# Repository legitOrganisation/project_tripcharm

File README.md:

# project_tripcharm

Github Repository containing all technical files in regard to our project.

v1-no-audio branch has been deprecated and merged to main branch.

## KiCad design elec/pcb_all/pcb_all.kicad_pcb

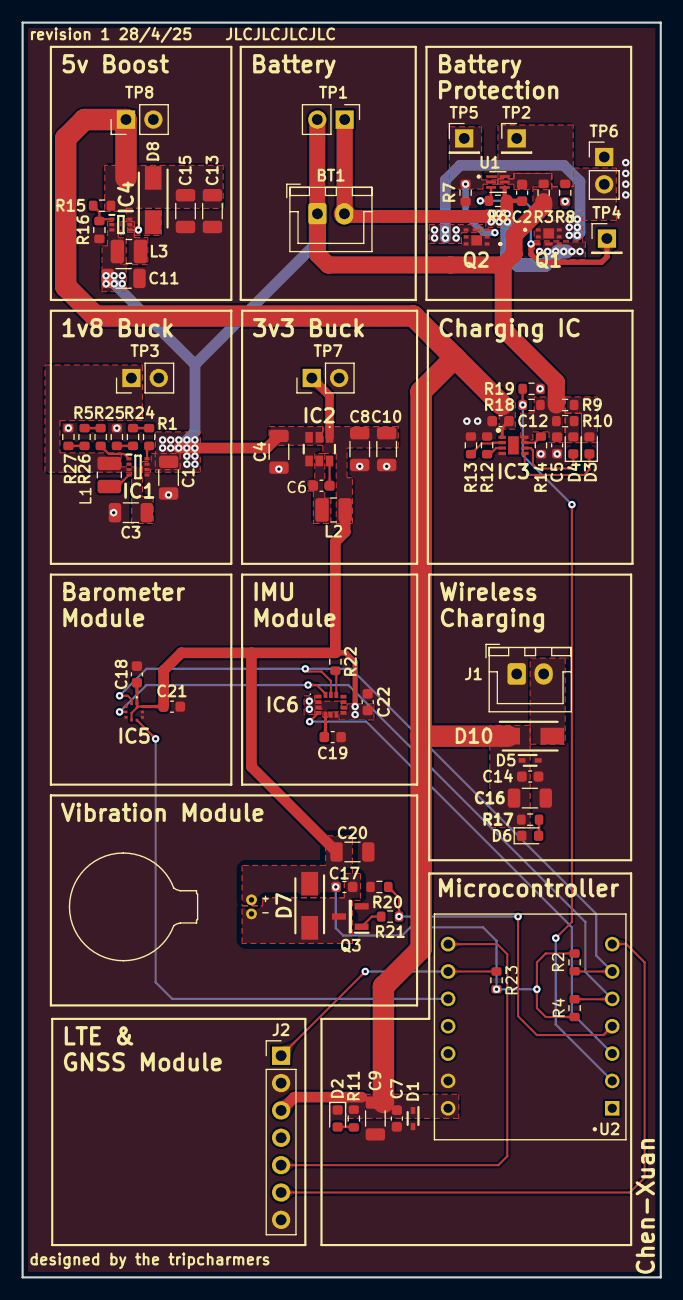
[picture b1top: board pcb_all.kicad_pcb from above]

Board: 2 copper layers, 59.2 x 116.5 mm, 84 parts (0 on the bottom side), 45 nets.

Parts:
B1: HD-EMC1003-3-LW27; PUI_HD-EMC1003-3-LW27
BT1: Battery_Cell; JST_XH_B2B-XH-A_1x02_P2.50mm_Vertical
C1: 4.7uF; C_1206_3216Metric
C2, C6, C7, C14, C17, C18, C19, C21, C22: 100nF; C_0603_1608Metric
C3, C8, C10, C13, C15, C20: 22uF; C_1206_3216Metric
C4, C9, C11, C16: 10uF; C_1206_3216Metric
C5, C12: 1uF; C_0603_1608Metric
D1, D5: ESD7351XV2T1G; SODFL1608X70N
D2, D3, D4, D6: LED; LED_0603_1608Metric
D7, D8, D10: SS14-M3_5AT; DIOM5127X229N
IC1: TPS629203QDRLRQ1; SOTFL50P160X60-8N
IC2: AP63203WU-7; AP63203WU7
IC3: BQ25176MDSGR; SON50P200X200X80-9N
IC4: TPS61023DRLR; SOTFL50P160X60-6N
IC5: BMP390
IC6: LSM6DSLTR
J1: Conn_01x02; JST_XH_B2B-XH-A_1x02_P2.50mm_Vertical
J2: Conn_01x07; PinHeader_1x07_P2.54mm_Vertical
L1: 2.2uH; L_1008_2520Metric
L2: 4.7uH; L_1008_2520Metric
L3: 1uH; L_1008_2520Metric
Q1, Q2: CSD16301Q2
Q3: IRLML6344TRPBF; SOT95P237X112-3N
R1, R5, R26: 30k; R_0603_1608Metric
R2, R4, R22, R27: 4.7k; R_0603_1608Metric
R3: R330; R_0603_1608Metric
R6, R7: 5.1M; R_0603_1608Metric
R8: 2.2K; R_0603_1608Metric
R9, R10, R12, R18, R20, R23: 10k; R_0603_1608Metric
R11, R17: 680R; R_0603_1608Metric
R13: 604R; R_0603_1608Metric
R14: 24.3k; R_0603_1608Metric
R15: 68k; R_0603_1608Metric
R16: 510k; R_0603_1608Metric
R19: 1k; R_0603_1608Metric
R21: 100R; R_0603_1608Metric
R24, R25: 2k; R_0603_1608Metric
TP1, TP3, TP6, TP7, TP8: TestPoint_2Pole; PinHeader_1x02_P2.54mm_Vertical
TP2, TP4, TP5: TestPoint; PinHeader_1x01_P2.54mm_Vertical
U1: BQ29700DSER; SON50P150X150X80-6N
U2: Xiao_ESP32-C3

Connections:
+1V8: C3.1, IC1.3 (VOS), L1.2, TP3.1
+3V3: B1.P, C8.1, C10.1, C17.1, C18.1, C19.1, C20.1, C21.1, C22.1, D7.1 (K), IC2.1 (FB), IC5.1 (VDDIO), IC5.6 (CSB), IC5.10 (VDD), IC6.2 (SDX), IC6.3 (SCX), IC6.5 (VDDIO), IC6.8 (VDD), L2.2, R2.1, R4.1, R22.1, R23.2, TP7.1
+5V: C7.1, C9.1, C12.1, C13.1, C14.1, C15.1, C16.1, D1.1 (K), D5.1 (K), D8.1 (K), D10.1 (K), IC3.1 (IN), J2.3, R11.1, R15.1, R17.1, TP8.1, U2.14 (VUSB)
+BATT: BT1.1 (+), C1.1, C4.1, C5.1, C11.1, IC1.6 (VIN), IC1.7 (EN), IC2.2 (EN), IC2.3 (VIN), IC3.8 (OUT), IC4.2 (EN), IC4.3 (VIN), L3.1, R3.1, R9.1, R10.1, R18.1, TP1.2, TP6.2
/BATT VOLTAGE: R18.2, R19.1, U2.2 (D1)
/INT1 (IMU): IC6.4 (INT1), U2.3 (D2)
/INT (BAROMETER): IC5.7 (INT), U2.10 (D9)
/PWM (Vibration): R20.1, R21.1, U2.4 (D3)
/RX (SIM7600G-H): J2.6, U2.7 (TX_D6)
/SCL: IC5.2 (SCK), IC6.13 (SCL), R2.2, U2.6 (D5)
/SDA: IC5.4 (SDI), IC6.14 (SDA), R4.2, U2.5 (D4)
/SLEEP (SIM7600G-H): J2.1, R23.1, U2.9 (D8)
/TX (SIM7600G-H): J2.5, U2.8 (RX_D7)
GND: C1.2, C3.2, C4.2, C5.2, C7.2, C8.2, C9.2, C10.2, C11.2, C12.2, C13.2, C14.2, C15.2, C16.2, C18.2, C19.2, C20.2, C21.2, C22.2, D1.2 (A), D2.1 (K), D5.2 (A), D6.1 (K), IC1.5 (GND), IC2.4 (GND), IC3.4 (GND), IC4.4 (GND), IC5.3 (VSS_1), IC5.5 (SDO), IC5.8 (VSS_2), IC5.9 (VSS_3), IC6.1 (SDO/SA0), IC6.6 (GND_1), IC6.7 (GND_2), J1.1, J2.2, J2.7, Q2.2 (D), Q3.2 (S), R7.2, R8.2, R12.2, R13.2, R14.2, R16.2, R19.2, R20.2, R25.2, R27.2, TP3.2, TP6.1, TP7.2, TP8.2, U2.13 (GND)
unnamed: BT1.2 (-), C2.2, Q1.1 (S), R6.1, TP1.1, U1.4 (VSS)
unnamed: D2.2 (A), R11.2
unnamed: D3.2 (A), R9.2
unnamed: D3.1 (K), IC3.5 (STAT)
unnamed: D4.2 (A), R10.2
unnamed: D4.1 (K), IC3.6 (~PG)
unnamed: D6.2 (A), R17.2
unnamed: B1.N, C17.2, D7.2 (A), Q3.3 (D)
unnamed: D8.2 (A), IC4.6 (VOUT)
unnamed: D10.2 (A), J1.2
unnamed: IC1.1 (FB/VSET), R5.1
unnamed: IC1.8 (MODE/S-CONF), R1.1
unnamed: IC1.4 (SW), L1.1
unnamed: C6.1, IC2.6 (BST)
unnamed: C6.2, IC2.5 (SW), L2.1
unnamed: IC3.3 (BIAS), R12.1
unnamed: IC3.2 (ISET), R13.1
unnamed: IC3.7 (VSET), R14.1
unnamed: IC4.1 (FB), R15.2, R16.1
unnamed: IC4.5 (SW), L3.2
unnamed: IC6.12 (CS), R22.2
unnamed: Q1.2 (D), Q2.1 (S)
unnamed: Q1.3 (G), R6.2, TP4.1, U1.3 (DOUT)
unnamed: Q2.3 (G), R7.1, TP5.1, U1.2 (COUT)
unnamed: Q3.1 (G), R21.2
unnamed: R1.2, R24.2
unnamed: R24.1, R25.1
unnamed: R26.1, R27.1
unnamed: R5.2, R26.2
unnamed: C2.1, R3.2, U1.5 (BAT)
unnamed: R8.1, TP2.1, U1.6 (V-)

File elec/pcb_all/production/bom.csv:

Designator,Footprint,Quantity,Value,LCSC Part #
B1,PUI_HD-EMC1003-3-LW27,1,HD-EMC1003-3-LW27,
BT1,JST_XH_B2B-XH-A_1x02_P2.50mm_Vertical,1,Battery_Cell,
C1,1206,1,4.7uF,
"C10, C13, C15, C20, C3, C8",1206,6,22uF,
"C11, C16, C4, C9",1206,4,10uF,
"C12, C5",0603,2,1uF,
"C14, C18, C19, C21, C22, C6, C7",0603,7,100nF,
"C17, C2",0603,2,0.1uF,
"D1, D5",SODFL1608X70N,2,ESD7351XV2T1G,
"D10, D7, D8",DIOM5127X229N,3,SS14-M3_5AT,
"D2, D3, D4, D6",0603,4,LED,
IC1,SOTFL50P160X60-8N,1,TPS629203QDRLRQ1,
IC2,AP63203WU7,1,AP63203WU-7,
IC3,SON50P200X200X80-9N,1,BQ25176MDSGR,
IC4,SOTFL50P160X60-6N,1,TPS61023DRLR,
IC5,BMP390,1,BMP390,
IC6,LSM6DSLTR,1,LSM6DSLTR,
J1,JST_XH_B2B-XH-A_1x02_P2.50mm_Vertical,1,Conn_01x02,
J2,PinHeader_1x07_P2.54mm_Vertical,1,Conn_01x07,
L1,1008,1,2.2uH,
L2,1008,1,4.7uH,
L3,1008,1,1uH,
"Q1, Q2",CSD16301Q2,2,CSD16301Q2,
Q3,SOT95P237X112-3N,1,IRLML6344TRPBF,
R1,0603,1,34k,
"R10, R12, R18, R20, R23, R9",0603,6,10k,
"R11, R17",0603,2,680R,
R13,0603,1,604,
R14,0603,1,24.3k,
R15,0603,1,732k,
R16,0603,1,100k,
R19,0603,1,1k,
"R2, R22, R4",0603,3,4.7k,
R21,0603,1,100R,
R3,0603,1,R330,
R5,0603,1,64.9k,
"R6, R7",0603,2,5.1M,
R8,0603,1,2.2K,
"TP1, TP3, TP6, TP7, TP8",PinHeader_1x02_P2.54mm_Vertical,5,TestPoint_2Pole,
"TP2, TP4, TP5",PinHeader_1x01_P2.54mm_Vertical,3,TestPoint,
U1,SON50P150X150X80-6N,1,BQ29700DSER,
U2,Xiao_ESP32-C3,1,Xiao_ESP32-C3,

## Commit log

2025-03-10 creatde pcb files
2025-03-11 began on schematics
2025-03-11 forgot to close project file
2025-03-12 did most pf power schematics
2025-03-12 did some stuff
2025-03-13 finished power (charging) schematics
2025-03-15 did 3v3 buck
2025-03-15 did 5v boost
2025-03-18 did imu, batt voltage monitoring, mic
2025-03-29 fixed an oopsie whihc owuld have been really bad
2025-03-29 uploaded new mech files
2025-03-30 uploaded pinheader step files, added renders
2025-04-03 uploaded render files
2025-04-20 did 1v8 buck, did imu and sim7600g-h module connection with imu
2025-04-20 did dsomse stuff
2025-04-20 added stuff
2025-04-24 cleaned up schematics, added vibration module components, pending drawing schematics
2025-04-25 did vibration module, pedning other stuff
2025-04-26 1st version schematics completed (hopefully)
2025-04-26 oops forgot to annotate schematic
2025-04-26 did pcb layout for bucks, boost, imu, barometer, vibration module, need to continue batt protection
2025-04-27 complaeted placement of all components, pending traces to mcu
2025-04-27 completed pcb?
2025-04-28 made some stuff look better
2025-04-28 cleaned up some more stuff
2025-04-28 made jlcdfm slightly happier
2025-04-28 added lcsc numbers for all components except resistors
2025-04-28 added resistors lcsc part no.
2025-04-28 update: bom
2025-04-28 completed most jlc part numbers, pending reduce number of extended & find replacement for 1v8 buck
2025-05-01 did stuff
2025-05-04 did some stuff?
2025-05-10 added sim7600g-h drivers
2025-06-08 wrote code and tested stuff
2025-06-20 addd github folder
2025-06-20 i did stuff
2025-07-19 allllmost done; just need to trace modules together
2025-07-20 some traces (3v3 and 5v)
2025-07-20 all done excpet pcba
2025-07-20 made dfm happy
2025-07-21 completed elec?
2025-07-21 updated page info
2025-07-23 fixed bom
2025-07-23 stuff
2025-07-28 changed code
2025-07-29 did code
2025-07-30 wrote code
2025-07-30 added readme
2025-07-31 wrote code becuz chatgpt dumb
2025-08-02 fixed code
2025-08-03 wrote code (send msg on button and fall detection)
2025-08-09 idk what i did
2025-08-09 kms2.0
2025-08-09 kms3.0
2025-08-09 deleted the zip
2025-08-09 wrote server code
2025-08-09 did gitignore
2025-08-09 kmskms
2025-08-09 uploaded app code
2025-08-09 did gitignore, deleted old app
2025-08-09 added cx workspace
2025-08-09 im dumb
2025-08-09 did sth
2025-08-09 changed server code
2025-08-09 wrote web-app code
2025-08-09 stuffed
2025-08-09 srtuffed?
2025-08-09 installed expressjs for web-app
2025-08-09 updated app
2025-08-09 added fall detection strength
2025-08-09 added back alert for vibrate
2025-08-09 wrote events code?
2025-08-10 geofence actually works!
2025-08-10 update queues
2025-08-10 added api key
2025-08-10 something?
2025-08-10 code
2025-08-10 made test console?
2025-08-10 updated test-console
2025-08-11 changed code?
2025-08-11 codes?
2025-08-11 Revert "code"
    This reverts commit 2fa0947c43e2376ed73f056bcbc8bc814987bf4a.
2025-08-11 code changed?
2025-08-11 new code
2025-08-11 fixed poll once?
2025-08-11 added marker to map
2025-08-11 wrote events code
2025-08-11 codes
2025-08-11 added saving geofencing to server
2025-08-11 deleted comment
2025-08-11 idk what chatgpt did
2025-08-11 minor bug fix
2025-08-11 marked uplaod gps as deprecated
2025-08-11 added logo for test console and web app
2025-08-11 made import and export slightly more similar
2025-08-11 added so commands clwear aft 5 min
2025-08-11 pruning for geofencing, gps, battery
2025-08-11 new device code
2025-08-11 added upload gps to api
2025-08-11 fixed gps coords
2025-08-11 device code with batt percentage and gps cooirds
2025-08-11 most sutff are there
2025-08-13 wrote code to get vibrate command
2025-08-14 vibratio works
2025-08-14 added vibration clearing code
